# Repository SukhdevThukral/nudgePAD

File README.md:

# nudgePAD (Hackpad)

learnt a lot of PCB making and :( took me A LOT of time to wrap my head around everything but it was fun 

# Inspiration
NOW HACKPAD is said to be the starting point of creating our OWN PCBs but i gave myself challenge later on in the journey to actually learn side by side rather than following the guide which i still love btw but was lwk vague (no offense <3)

# Specifications

BOM has also been uploaded ;D

<h3>Schematic-</h3>

<h3>PCB (3D)-</h3>

<h3>PCB</h3>

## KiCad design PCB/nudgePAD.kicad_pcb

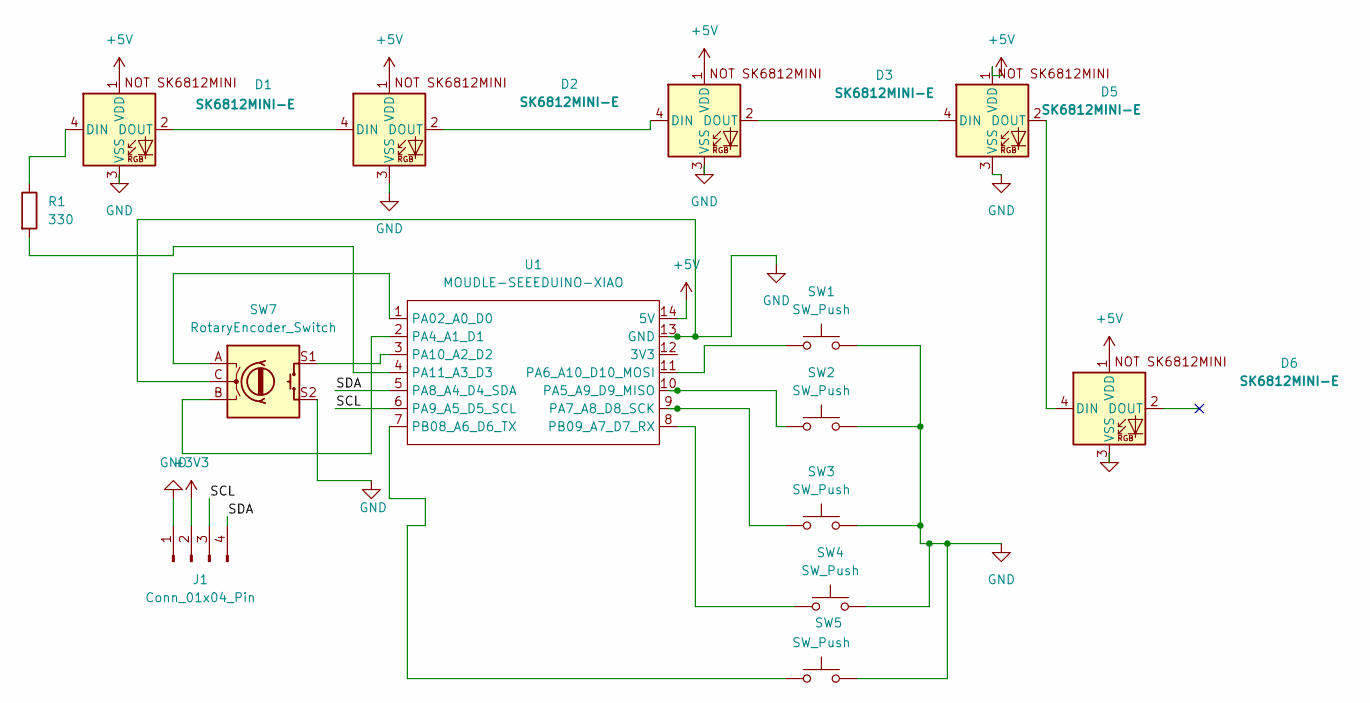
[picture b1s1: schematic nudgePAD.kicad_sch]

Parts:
D1, D2, D3, D5, D6: SK6812MINI-E; SK6812MINI-E_fixed
J1: Conn_01x04_Pin; SSD1306-0.91-OLED-4pin-128x32
R1: 330; R_0805_2012Metric
SW1, SW2, SW3, SW4, SW5: SW_Push; SW_Cherry_MX_1.00u_PCB
SW7: RotaryEncoder_Switch; RotaryEncoder_Alps_EC11E-Switch_Vertical_H20mm
U1: MOUDLE-SEEEDUINO-XIAO; XIAO-Generic-Hybrid-14P-2.54-21X17.8MM

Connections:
+3V3: J1.2
+5V: D1.1 (VDD), D2.1 (VDD), D3.1 (VDD), D5.1 (VDD), D6.1 (VDD), U1.14 (5V)
/SCL: J1.3, U1.6 (PA9_A5_D5_SCL)
/SDA: J1.4, U1.5 (PA8_A4_D4_SDA)
GND: D1.3 (VSS), D2.3 (VSS), D3.3 (VSS), D5.3 (VSS), D6.3 (VSS), J1.1, SW1.2, SW2.2, SW3.2, SW4.2, SW5.2, SW7.C, SW7.S2, U1.13 (GND)
unnamed: D1.4 (DIN), R1.1
unnamed: D1.2 (DOUT), D2.4 (DIN)
unnamed: D2.2 (DOUT), D3.4 (DIN)
unnamed: D3.2 (DOUT), D5.4 (DIN)
unnamed: D5.2 (DOUT), D6.4 (DIN)
unnamed: SW7.A, U1.1 (PA02_A0_D0)
unnamed: SW7.B, U1.2 (PA4_A1_D1)
unnamed: SW2.1, U1.10 (PA5_A9_D9_MISO)
unnamed: SW1.1, U1.11 (PA6_A10_D10_MOSI)
unnamed: SW3.1, U1.9 (PA7_A8_D8_SCK)
unnamed: SW7.S1, U1.3 (PA10_A2_D2)
unnamed: R1.2, U1.4 (PA11_A3_D3)
unnamed: SW5.1, U1.7 (PB08_A6_D6_TX)
unnamed: SW4.1, U1.8 (PB09_A7_D7_RX)

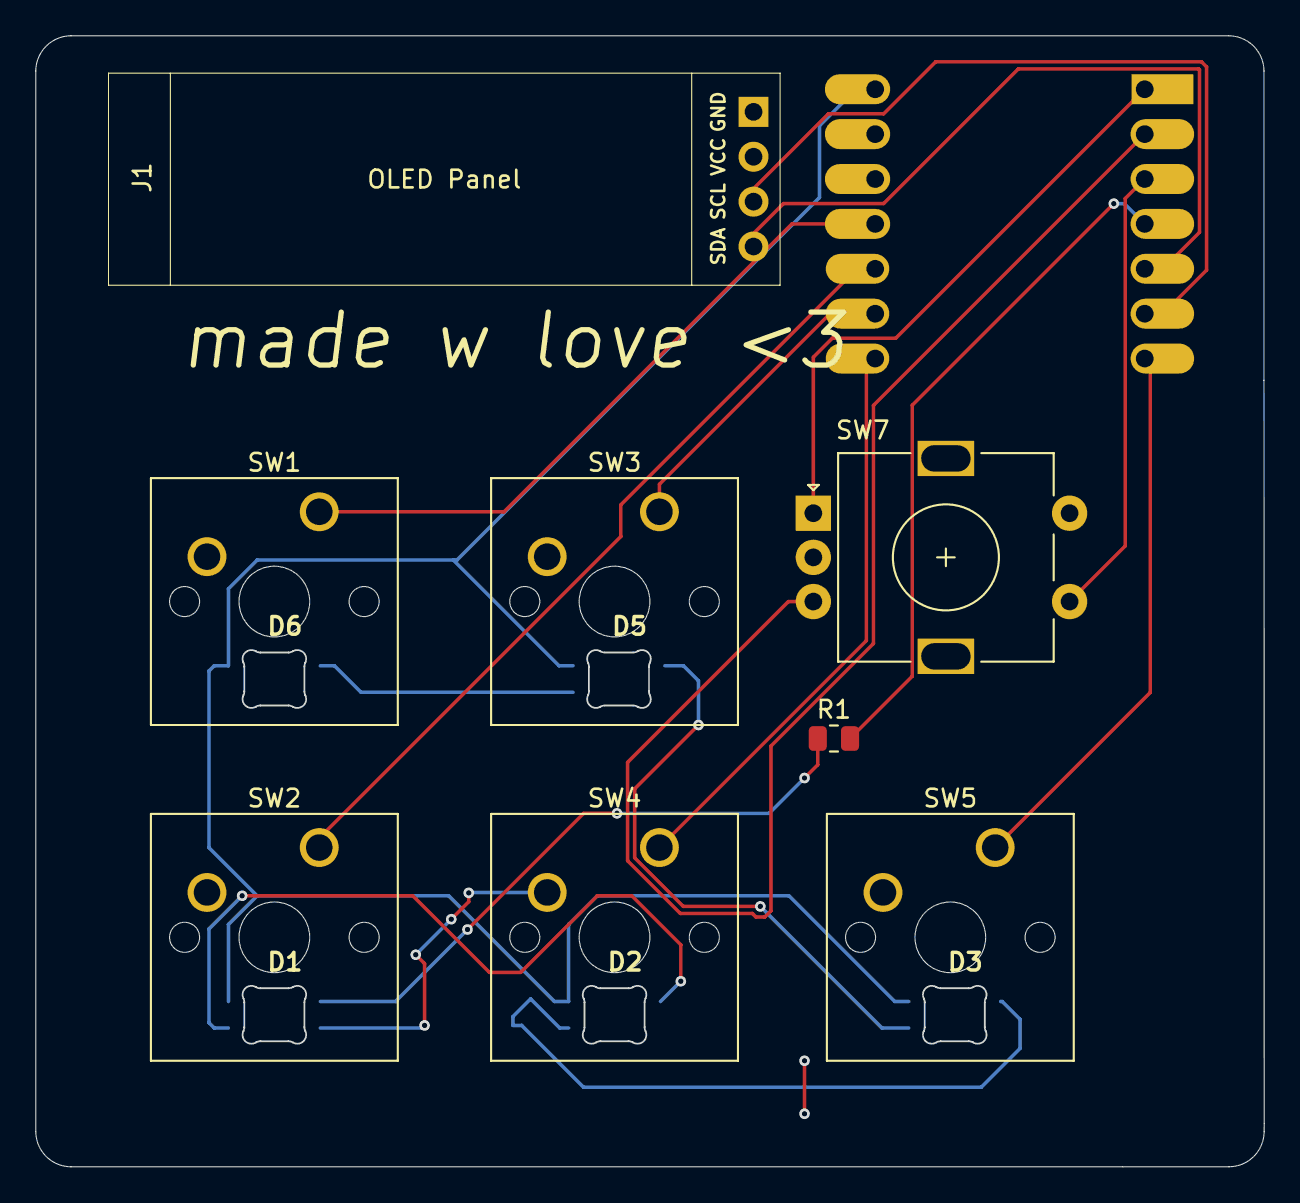
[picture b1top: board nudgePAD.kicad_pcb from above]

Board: 2 copper layers, 69.5 x 64.0 mm, 14 parts (1 on the bottom side), 18 nets.
